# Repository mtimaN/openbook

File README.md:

# openbook

## Overview

# 📚 eBook Reader – System Overview

This project is an eBook reader based on the ESP32-C3 microcontroller. It features a 7.5" E-Ink display, SD card storage, environmental sensing, and a rechargeable LiPo battery, all optimized for low power consumption and readability.

### **ESP32-C3 WROOM**
The main microcontroller that handles:
- Display updates via **SPI**
- File system and memory management
- Button inputs through **GPIO**
- Communication with sensors and RTC via **I2C**
- USB communication for firmware updates or data transfer

### **E-Ink DISPLAY 7.5" 800x400**
- Ultra-low power display ideal for reading in bright light
- Interface: SPI
- Controlled by the ESP32 for rendering text and images

###  Storage

- **SD Card**: Stores eBooks and data files
- **External NOR Flash**: Used for firmware, fonts, or static assets

### Power Management

- **USB-C**: Input for charging and potential USB data connection
- **Battery Charger (MCP73831)**: Manages LiPo charging
- **LiPo Battery**: Powers the system when unplugged
- **Battery Level Monitor (MAX17048G+T10)**: Reports battery percentage to the ESP32
- **3V3 LDO Regulator**: Provides stable 3.3V for the system

### **BME688 Sensor**
- Measures:
  - Temperature
  - Humidity
  - Pressure
  - Air quality
- Data can be displayed or logged for contextual awareness

### **DS3231SN RTC Module**
- Keeps track of time even when powered off
- Useful for:
  - Timestamps
  - Scheduled wake-ups
  - Time-based features
## ⚡ Energy Usage Overview

Estimated average current during typical reading:

| Component        | Avg Current | Notes                             |
|------------------|-------------|-----------------------------------|
| ESP32-C3         | ~2 mA       | Light sleep + brief active use    |
| E-Ink Display    | ~1–2 mA     | Only draws power during refresh   |
| SD Card          | ~1 mA       | Accessed briefly per page turn    |
| BME688 Sensor    | ~0.15 mA    | In low-power mode                 |
| RTC DS3231SN     | ~0.002 mA   | Always running                    |
| Battery Monitor  | ~0.05 mA    | Very low power                    |
| **Total**        | **~5.2 mA** | Approximate average current       |

With a **1200 mAh LiPo battery**:
- **Estimated runtime:** ~**9 days** of light usage
- Based on 1 screen update per minute, minimal background activity

## Bill of Materials (BOM) 
|SAMACSYS_PARTS_USB4110GFA|Value                                                                         |Device                                                                        |Detailed Description                                                                                                                                                                                                                                                                                                                                                                                                                                                                                |Link                                                                                                                         |
|-------------------------|------------------------------------------------------------------------------|------------------------------------------------------------------------------|----------------------------------------------------------------------------------------------------------------------------------------------------------------------------------------------------------------------------------------------------------------------------------------------------------------------------------------------------------------------------------------------------------------------------------------------------------------------------------------------------|-----------------------------------------------------------------------------------------------------------------------------|
|BOOT_BUTTON              |BUTTON_CUSYOMV1                                                               |BUTTON_CUSYOMV1                                                               |                                                                                                                                                                                                                                                                                                                                                                                                                                                                                                    |https://industry.panasonic.com/global/en/products/control/switch/light-touch/number/evqpuj02k                                |
|C1                       |100nF                                                                         |ESP32_WROVER_EAGLE-LTSPICE_CC0402                                             |CAPACITOR, European symbol                                                                                                                                                                                                                                                                                                                                                                                                                                                                          |https://ro.mouser.com/ProductDetail/KYOCERA-AVX/12107C104KAT2A?qs=%252BdQmOuGyFcEpzvTfYF11Tg%3D%3D                           |
|C1_BAT                   |4.7uF                                                                         |ESP32_WROVER_EAGLE-LTSPICE_CC0402                                             |CAPACITOR, European symbol                                                                                                                                                                                                                                                                                                                                                                                                                                                                          |https://ro.mouser.com/ProductDetail/KYOCERA-AVX/12107C104KAT2A?qs=%252BdQmOuGyFcEpzvTfYF11Tg%3D%3D                           |
|C1_BAT1                  |4.7uF                                                                         |ESP32_WROVER_EAGLE-LTSPICE_CC0402                                             |CAPACITOR, European symbol                                                                                                                                                                                                                                                                                                                                                                                                                                                                          |https://ro.mouser.com/ProductDetail/KYOCERA-AVX/12107C104KAT2A?qs=%252BdQmOuGyFcEpzvTfYF11Tg%3D%3D                           |
|C1_BAT2                  |4.7uF                                                                         |EAGLE-LTSPICE_CC0402                                                          |CAPACITOR, European symbol                                                                                                                                                                                                                                                                                                                                                                                                                                                                          |https://ro.mouser.com/ProductDetail/KYOCERA-AVX/12107C104KAT2A?qs=%252BdQmOuGyFcEpzvTfYF11Tg%3D%3D                           |
|C2                       |100nF                                                                         |ESP32_WROVER_EAGLE-LTSPICE_CC0402                                             |CAPACITOR, European symbol                                                                                                                                                                                                                                                                                                                                                                                                                                                                          |https://ro.mouser.com/ProductDetail/KYOCERA-AVX/12107C104KAT2A?qs=%252BdQmOuGyFcEpzvTfYF11Tg%3D%3D                           |
|C2_BAT                   |4.7uF                                                                         |ESP32_WROVER_EAGLE-LTSPICE_CC0402                                             |CAPACITOR, European symbol                                                                                                                                                                                                                                                                                                                                                                                                                                                                          |https://ro.mouser.com/ProductDetail/KYOCERA-AVX/12107C104KAT2A?qs=%252BdQmOuGyFcEpzvTfYF11Tg%3D%3D                           |
|C3                       |100uF TANT                                                                    |RCL_CPOL-EUCT3528                                                             |POLARIZED CAPACITOR, European symbol                                                                                                                                                                                                                                                                                                                                                                                                                                                                |https://ro.mouser.com/ProductDetail/Panasonic/EEU-FS1K101L?qs=sGAEpiMZZMvwFf0viD3Y3fHxNcSaiftwbgqrEa58hlq7Mz20qWHEdw%3D%3D   |
|C4                       |4.7uF/25V                                                                     |ESP32_WROVER_EAGLE-LTSPICE_CC0402                                             |CAPACITOR, European symbol                                                                                                                                                                                                                                                                                                                                                                                                                                                                          |https://ro.mouser.com/ProductDetail/KYOCERA-AVX/12107C104KAT2A?qs=%252BdQmOuGyFcEpzvTfYF11Tg%3D%3D                           |
|C4_USB                   |100nF                                                                         |ESP32_WROVER_EAGLE-LTSPICE_CC0402                                             |CAPACITOR, European symbol                                                                                                                                                                                                                                                                                                                                                                                                                                                                          |https://ro.mouser.com/ProductDetail/KYOCERA-AVX/12107C104KAT2A?qs=%252BdQmOuGyFcEpzvTfYF11Tg%3D%3D                           |
|C5                       |1uF                                                                           |ESP32_WROVER_EAGLE-LTSPICE_CC0402                                             |CAPACITOR, European symbol                                                                                                                                                                                                                                                                                                                                                                                                                                                                          |https://ro.mouser.com/ProductDetail/KYOCERA-AVX/12107C104KAT2A?qs=%252BdQmOuGyFcEpzvTfYF11Tg%3D%3D                           |
|C5_USB                   |4.7uF                                                                         |ESP32_WROVER_EAGLE-LTSPICE_CC0402                                             |CAPACITOR, European symbol                                                                                                                                                                                                                                                                                                                                                                                                                                                                          |https://ro.mouser.com/ProductDetail/KYOCERA-AVX/12107C104KAT2A?qs=%252BdQmOuGyFcEpzvTfYF11Tg%3D%3D                           |
|C6                       |100nF                                                                         |ESP32_WROVER_EAGLE-LTSPICE_CC0402                                             |CAPACITOR, European symbol                                                                                                                                                                                                                                                                                                                                                                                                                                                                          |https://ro.mouser.com/ProductDetail/KYOCERA-AVX/12107C104KAT2A?qs=%252BdQmOuGyFcEpzvTfYF11Tg%3D%3D                           |
|C7                       |10uF                                                                          |ESP32_WROVER_EAGLE-LTSPICE_CC0402                                             |CAPACITOR, European symbol                                                                                                                                                                                                                                                                                                                                                                                                                                                                          |https://ro.mouser.com/ProductDetail/KYOCERA-AVX/12107C104KAT2A?qs=%252BdQmOuGyFcEpzvTfYF11Tg%3D%3D                           |
|C8                       |100nF                                                                         |ESP32_WROVER_EAGLE-LTSPICE_CC0402                                             |CAPACITOR, European symbol                                                                                                                                                                                                                                                                                                                                                                                                                                                                          |https://ro.mouser.com/ProductDetail/KYOCERA-AVX/12107C104KAT2A?qs=%252BdQmOuGyFcEpzvTfYF11Tg%3D%3D                           |
|C9                       |100nF                                                                         |EAGLE-LTSPICE_CC0402                                                          |CAPACITOR, European symbol                                                                                                                                                                                                                                                                                                                                                                                                                                                                          |https://ro.mouser.com/ProductDetail/KYOCERA-AVX/12107C104KAT2A?qs=%252BdQmOuGyFcEpzvTfYF11Tg%3D%3D                           |
|C10                      |100nF                                                                         |ESP32_WROVER_EAGLE-LTSPICE_CC0402                                             |CAPACITOR, European symbol                                                                                                                                                                                                                                                                                                                                                                                                                                                                          |https://ro.mouser.com/ProductDetail/KYOCERA-AVX/12107C104KAT2A?qs=%252BdQmOuGyFcEpzvTfYF11Tg%3D%3D                           |
|C10_SUPERCAP             |CPH3225A                                                                      |CPH3225A                                                                      |Cap 0.011F 3.3V 1210 Flat                                                                                                                                                                                                                                                                                                                                                                                                                                                                           |https://ro.mouser.com/ProductDetail/Seiko-Semiconductors/CPH3225A?qs=3etwrb1wR%252BhUOph6lAO7eg%3D%3D                        |
|CHANGE_BUTTON            |BUTTON_CUSYOMV1                                                               |BUTTON_CUSYOMV1                                                               |                                                                                                                                                                                                                                                                                                                                                                                                                                                                                                    |https://industry.panasonic.com/global/en/products/control/switch/light-touch/number/evqpuj02k                                |
|CHG_LED                  |                                                                              |ADAFRUIT_LEDCHIP-LED0603                                                      |LED                                                                                                                                                                                                                                                                                                                                                                                                                                                                                                 |https://ro.mouser.com/ProductDetail/BJB/35.116.1007-001-01?qs=iLKYxzqNS76jqQb6thkyzg%3D%3D                                   |
|C_DELAY                  |100nF                                                                         |ESP32_WROVER_EAGLE-LTSPICE_CC0402                                             |CAPACITOR, European symbol                                                                                                                                                                                                                                                                                                                                                                                                                                                                          |https://ro.mouser.com/ProductDetail/KYOCERA-AVX/12107C104KAT2A?qs=%252BdQmOuGyFcEpzvTfYF11Tg%3D%3D                           |
|D1                       |USBLC6-2SC6Y                                                                  |USBLC6-2SC6Y                                                                  |Low Cap. ESD Protection Auto SOT-23-6 STMicroelectronics USBLC6-2SC6Y, Dual Uni-Directional TVS Diode Array, 6-Pin SOT-23                                                                                                                                                                                                                                                                                                                                                                           |https://ro.mouser.com/ProductDetail/Nexperia/PMEG6030AEXEX?qs=olJun0bQHM8zqhEtOgE2ZA%3D%3D                                   |
|D2                       |ESP32_WROVER_AVX---SD0805S020S1R0_AVX_SD0805S020S1R0_0_0AVX_SD0805S020S1R0_0_0|ESP32_WROVER_AVX---SD0805S020S1R0_AVX_SD0805S020S1R0_0_0AVX_SD0805S020S1R0_0_0|Schottky Barrier Rectifier Diode                                                                                                                                                                                                                                                                                                                                                                                                                                                                    |https://ro.mouser.com/ProductDetail/Nexperia/PMEG6030AEXEX?qs=olJun0bQHM8zqhEtOgE2ZA%3D%3D                                   |
|D3                       |MBR0530                                                                       |MBR0530                                                                       |ON SEMICONDUCTOR - MBR0530 - DIODE, SCHOTTKY, 0.5A, 30V, SOD-123                                                                                                                                                                                                                                                                                                                                                                                                                                    |https://ro.mouser.com/ProductDetail/Nexperia/PMEG6030AEXEX?qs=olJun0bQHM8zqhEtOgE2ZA%3D%3D                                   |
|D4                       |MBR0530                                                                       |MBR0530                                                                       |ON SEMICONDUCTOR - MBR0530 - DIODE, SCHOTTKY, 0.5A, 30V, SOD-123                                                                                                                                                                                                                                                                                                                                                                                                                                    |https://ro.mouser.com/ProductDetail/Nexperia/PMEG6030AEXEX?qs=olJun0bQHM8zqhEtOgE2ZA%3D%3D                                   |
|D5                       |MBR0530                                                                       |MBR0530                                                                       |ON SEMICONDUCTOR - MBR0530 - DIODE, SCHOTTKY, 0.5A, 30V, SOD-123                                                                                                                                                                                                                                                                                                                                                                                                                                    |https://ro.mouser.com/ProductDetail/Nexperia/PMEG6030AEXEX?qs=olJun0bQHM8zqhEtOgE2ZA%3D%3D                                   |
|D6                       |PGB1010603MR                                                                  |PGB1010603MR                                                                  |Check availability                                                                                                                                                                                                                                                                                                                                                                                                                                                                                  |https://ro.mouser.com/ProductDetail/Nexperia/PMEG6030AEXEX?qs=olJun0bQHM8zqhEtOgE2ZA%3D%3D                                   |
|D7                       |ESP32_WROVER_AVX---SD0805S020S1R0_AVX_SD0805S020S1R0_0_0AVX_SD0805S020S1R0_0_0|ESP32_WROVER_AVX---SD0805S020S1R0_AVX_SD0805S020S1R0_0_0AVX_SD0805S020S1R0_0_0|Schottky Barrier Rectifier Diode                                                                                                                                                                                                                                                                                                                                                                                                                                                                    |https://ro.mouser.com/ProductDetail/Nexperia/PMEG6030AEXEX?qs=olJun0bQHM8zqhEtOgE2ZA%3D%3D                                   |
|D8                       |PGB1010603MR                                                                  |PGB1010603MR                                                                  |Schottky Barrier Rectifier Diode                                                                                                                                                                                                                                                                                                                                                                                                                                                                    |https://ro.mouser.com/ProductDetail/Nexperia/PMEG6030AEXEX?qs=olJun0bQHM8zqhEtOgE2ZA%3D%3D                                   |
|D9                       |PGB1010603MR                                                                  |PGB1010603MR                                                                  |Schottky Barrier Rectifier Diode                                                                                                                                                                                                                                                                                                                                                                                                                                                                    |https://ro.mouser.com/ProductDetail/Nexperia/PMEG6030AEXEX?qs=olJun0bQHM8zqhEtOgE2ZA%3D%3D                                   |
|D10                      |PGB1010603MR                                                                  |PGB1010603MR                                                                  |Schottky Barrier Rectifier Diode                                                                                                                                                                                                                                                                                                                                                                                                                                                                    |https://ro.mouser.com/ProductDetail/Nexperia/PMEG6030AEXEX?qs=olJun0bQHM8zqhEtOgE2ZA%3D%3D                                   |
|D11                      |PGB1010603MR                                                                  |PGB1010603MR                                                                  |Schottky Barrier Rectifier Diode                                                                                                                                                                                                                                                                                                                                                                                                                                                                    |https://ro.mouser.com/ProductDetail/Nexperia/PMEG6030AEXEX?qs=olJun0bQHM8zqhEtOgE2ZA%3D%3D                                   |
|D12                      |PGB1010603MR                                                                  |PGB1010603MR                                                                  |Schottky Barrier Rectifier Diode                                                                                                                                                                                                                                                                                                                                                                                                                                                                    |https://ro.mouser.com/ProductDetail/Nexperia/PMEG6030AEXEX?qs=olJun0bQHM8zqhEtOgE2ZA%3D%3D                                   |
|EPD_C1                   |1uF/50V                                                                       |ESP32_WROVER_EAGLE-LTSPICE_CC0402                                             |CAPACITOR, European symbol                                                                                                                                                                                                                                                                                                                                                                                                                                                                          |https://ro.mouser.com/ProductDetail/KEMET/MMK10105K50A01L4BULK?qs=IKDMbYZLynBqWdM%252BAUSFtw%3D%3D                           |
|EPD_C2                   |1uF/50V                                                                       |ESP32_WROVER_EAGLE-LTSPICE_CC0402                                             |CAPACITOR, European symbol                                                                                                                                                                                                                                                                                                                                                                                                                                                                          |https://ro.mouser.com/ProductDetail/KEMET/MMK10105K50A01L4BULK?qs=IKDMbYZLynBqWdM%252BAUSFtw%3D%3D                           |
|EPD_C5                   |1uF/50V                                                                       |ESP32_WROVER_EAGLE-LTSPICE_CC0402                                             |CAPACITOR, European symbol                                                                                                                                                                                                                                                                                                                                                                                                                                                                          |https://ro.mouser.com/ProductDetail/KEMET/MMK10105K50A01L4BULK?qs=IKDMbYZLynBqWdM%252BAUSFtw%3D%3D                           |
|EPD_C6                   |1uF/50V                                                                       |ESP32_WROVER_EAGLE-LTSPICE_CC0402                                             |CAPACITOR, European symbol                                                                                                                                                                                                                                                                                                                                                                                                                                                                          |https://ro.mouser.com/ProductDetail/KEMET/MMK10105K50A01L4BULK?qs=IKDMbYZLynBqWdM%252BAUSFtw%3D%3D                           |
|EPD_C7                   |1uF/50V                                                                       |ESP32_WROVER_EAGLE-LTSPICE_CC0402                                             |CAPACITOR, European symbol                                                                                                                                                                                                                                                                                                                                                                                                                                                                          |https://ro.mouser.com/ProductDetail/KEMET/MMK10105K50A01L4BULK?qs=IKDMbYZLynBqWdM%252BAUSFtw%3D%3D                           |
|EPD_C8                   |1uF/50V                                                                       |ESP32_WROVER_EAGLE-LTSPICE_CC0402                                             |CAPACITOR, European symbol                                                                                                                                                                                                                                                                                                                                                                                                                                                                          |https://ro.mouser.com/ProductDetail/KEMET/MMK10105K50A01L4BULK?qs=IKDMbYZLynBqWdM%252BAUSFtw%3D%3D                           |
|EPD_C9                   |1uF/50V                                                                       |ESP32_WROVER_EAGLE-LTSPICE_CC0402                                             |CAPACITOR, European symbol                                                                                                                                                                                                                                                                                                                                                                                                                                                                          |https://ro.mouser.com/ProductDetail/KEMET/MMK10105K50A01L4BULK?qs=IKDMbYZLynBqWdM%252BAUSFtw%3D%3D                           |
|EPD_C10                  |1uF/50V                                                                       |ESP32_WROVER_EAGLE-LTSPICE_CC0402                                             |CAPACITOR, European symbol                                                                                                                                                                                                                                                                                                                                                                                                                                                                          |https://ro.mouser.com/ProductDetail/KEMET/MMK10105K50A01L4BULK?qs=IKDMbYZLynBqWdM%252BAUSFtw%3D%3D                           |
|EPD_C11                  |1uF/50V                                                                       |ESP32_WROVER_EAGLE-LTSPICE_CC0402                                             |CAPACITOR, European symbol                                                                                                                                                                                                                                                                                                                                                                                                                                                                          |https://ro.mouser.com/ProductDetail/KEMET/MMK10105K50A01L4BULK?qs=IKDMbYZLynBqWdM%252BAUSFtw%3D%3D                           |
|EPD_C12                  |1uF/50V                                                                       |ESP32_WROVER_EAGLE-LTSPICE_CC0402                                             |CAPACITOR, European symbol                                                                                                                                                                                                                                                                                                                                                                                                                                                                          |https://ro.mouser.com/ProductDetail/KEMET/MMK10105K50A01L4BULK?qs=IKDMbYZLynBqWdM%252BAUSFtw%3D%3D                           |
|IC1                      |BD5229G-TR                                                                    |BD5229G-TR                                                                    |Voltage Detector with Adjustable Delay Time: CMOS processes are utilized to develop high precision, low current consumption CMOS reset ICs that allow arbitrary setting of the delay time. The extensive lineup includes both Nch Open Drain and CMOS output types in a wide range of detection voltages (from 2.3V to 6.0V, in 0.1V steps), enabling selection of the ideal solution based on customer requirements. In addition, the entire series is of course both lead-free and RoHS-compliant.|https://ro.mouser.com/ProductDetail/ROHM-Semiconductor/BD5229G-TR?qs=4kLU8WoGk0vvnhrrYwdszw%3D%3D                            |
|IC4                      |XC6220A331MR-G                                                                |XC6220A331MR-G                                                                |LDO Voltage Regulators                                                                                                                                                                                                                                                                                                                                                                                                                                                                              |                                                                                                                             |
|J1                       |FH34SRJ-24S-0.5SH_99_                                                         |FH34SRJ-24S-0.5SH_99_                                                         |24 Position FFC, FPC Connector Contacts, Top and Bottom 0.020 (0.50mm) Surface Mount, Right Angle"                                                                                                                                                                                                                                                                                                                                                                                                  |                                                                                                                             |
|J2                       |SAMACSYS_PARTS_USB4110-GF-A                                                   |SAMACSYS_PARTS_USB4110-GF-A                                                   |CONN USB 2.0 TYPE-C R/A SMT                                                                                                                                                                                                                                                                                                                                                                                                                                                                         |                                                                                                                             |
|J3                       |QWIIC_RIGHT_ANGLE                                                             |QWIIC_CONNECTORJS-1MM                                                         |SparkFun I2C Standard Qwiic Connector                                                                                                                                                                                                                                                                                                                                                                                                                                                               |                                                                                                                             |
|J4                       |112A-TAAR-R03_ATTEND                                                          |112A-TAAR-R03_ATTEND                                                          |Micro SD Card Socket, Push-Push Type, Top Mount, SMT, H=1.83mm, 10u                                                                                                                                                                                                                                                                                                                                                                                                                                 |                                                                                                                             |
|L1                       |68uH                                                                          |744043680IND_4828-WE-TPC_WRE                                                  |                                                                                                                                                                                                                                                                                                                                                                                                                                                                                                    |                                                                                                                             |
|PFMF.050.1               |ESP32C6_VARISTORCN1812                                                        |ESP32C6_VARISTORCN1812                                                        |VARISTOR                                                                                                                                                                                                                                                                                                                                                                                                                                                                                            |                                                                                                                             |
|Q1                       |20V/4.2A/52mO/1.4W                                                            |ESP32_WROVER_SPARKFUN-DISCRETESEMI_MOSFET_PCH-DMG2305UX-7                     |P-channel MOSFETs                                                                                                                                                                                                                                                                                                                                                                                                                                                                                   |                                                                                                                             |
|Q2                       |20V/4.2A/52mO/1.4W                                                            |ESP32_WROVER_SPARKFUN-DISCRETESEMI_MOSFET_PCH-DMG2305UX-7                     |P-channel MOSFETs                                                                                                                                                                                                                                                                                                                                                                                                                                                                                   |https://ro.mouser.com/ProductDetail/Vishay-Siliconix/SQ3425CEV-T1_GE3?qs=i8QVZAFTkqQazbKSzWc2Vg%3D%3D                        |
|Q3                       |SI1308EDL-T1-GE3                                                              |SI1308EDL-T1-GE3                                                              |MOSFET N-Ch 30V 1.5A TrenchFET SC70 Vishay Si1308EDL-T1-GE3 N-channel MOSFET Transistor, 1.5 A, 30 V, 3-Pin SC-70                                                                                                                                                                                                                                                                                                                                                                                   |https://ro.mouser.com/ProductDetail/Vishay-Semiconductors/SI1308EDL-T1-GE3?qs=bX1%252BNvsK%2FBramh9tgpOaEw%3D%3D             |
|R1                       |10K                                                                           |ESP32_WROVER_EAGLE-LTSPICE_RR0402                                             |RESISTOR, European symbol                                                                                                                                                                                                                                                                                                                                                                                                                                                                           |https://ro.mouser.com/ProductDetail/Vishay-Beyschlag/MCS0402MD4703BE500?qs=sGAEpiMZZMtlubZbdhIBIE4nSA98ICq40rObWhdYP%252BY%3D|
|R1-PINH                  |10K                                                                           |ESP32_WROVER_EAGLE-LTSPICE_RR0402                                             |RESISTOR, European symbol                                                                                                                                                                                                                                                                                                                                                                                                                                                                           |https://ro.mouser.com/ProductDetail/Vishay-Beyschlag/MCS0402MD4703BE500?qs=sGAEpiMZZMtlubZbdhIBIE4nSA98ICq40rObWhdYP%252BY%3D|
|R1-PINH1                 |10K                                                                           |ESP32_WROVER_EAGLE-LTSPICE_RR0402                                             |RESISTOR, European symbol                                                                                                                                                                                                                                                                                                                                                                                                                                                                           |https://ro.mouser.com/ProductDetail/Vishay-Beyschlag/MCS0402MD4703BE500?qs=sGAEpiMZZMtlubZbdhIBIE4nSA98ICq40rObWhdYP%252BY%3D|
|R1_BAT                   |200                                                                           |ESP32_WROVER_EAGLE-LTSPICE_RR0402                                             |RESISTOR, European symbol                                                                                                                                                                                                                                                                                                                                                                                                                                                                           |https://ro.mouser.com/ProductDetail/Vishay-Beyschlag/MCS0402MD4703BE500?qs=sGAEpiMZZMtlubZbdhIBIE4nSA98ICq40rObWhdYP%252BY%3D|
|R1_PWRUSB                |100K                                                                          |ESP32_WROVER_EAGLE-LTSPICE_RR0402                                             |RESISTOR, European symbol                                                                                                                                                                                                                                                                                                                                                                                                                                                                           |https://ro.mouser.com/ProductDetail/Vishay-Beyschlag/MCS0402MD4703BE500?qs=sGAEpiMZZMtlubZbdhIBIE4nSA98ICq40rObWhdYP%252BY%3D|
|R2                       |2.2                                                                           |ESP32_WROVER_EAGLE-LTSPICE_RR0402                                             |RESISTOR, European symbol                                                                                                                                                                                                                                                                                                                                                                                                                                                                           |https://ro.mouser.com/ProductDetail/Vishay-Beyschlag/MCS0402MD4703BE500?qs=sGAEpiMZZMtlubZbdhIBIE4nSA98ICq40rObWhdYP%252BY%3D|
|R2-PINH                  |10K                                                                           |ESP32_WROVER_EAGLE-LTSPICE_RR0402                                             |RESISTOR, European symbol                                                                                                                                                                                                                                                                                                                                                                                                                                                                           |https://ro.mouser.com/ProductDetail/Vishay-Beyschlag/MCS0402MD4703BE500?qs=sGAEpiMZZMtlubZbdhIBIE4nSA98ICq40rObWhdYP%252BY%3D|
|R2-PINH1                 |10K                                                                           |ESP32_WROVER_EAGLE-LTSPICE_RR0402                                             |RESISTOR, European symbol                                                                                                                                                                                                                                                                                                                                                                                                                                                                           |https://ro.mouser.com/ProductDetail/Vishay-Beyschlag/MCS0402MD4703BE500?qs=sGAEpiMZZMtlubZbdhIBIE4nSA98ICq40rObWhdYP%252BY%3D|
|R2-USB                   |5k1                                                                           |ESP32_WROVER_EAGLE-LTSPICE_RR0402                                             |RESISTOR, European symbol                                                                                                                                                                                                                                                                                                                                                                                                                                                                           |https://ro.mouser.com/ProductDetail/Vishay-Beyschlag/MCS0402MD4703BE500?qs=sGAEpiMZZMtlubZbdhIBIE4nSA98ICq40rObWhdYP%252BY%3D|
|R2-USB1                  |5k1                                                                           |ESP32_WROVER_EAGLE-LTSPICE_RR0402                                             |RESISTOR, European symbol                                                                                                                                                                                                                                                                                                                                                                                                                                                                           |https://ro.mouser.com/ProductDetail/Vishay-Beyschlag/MCS0402MD4703BE500?qs=sGAEpiMZZMtlubZbdhIBIE4nSA98ICq40rObWhdYP%252BY%3D|
|R2_BAT                   |2K                                                                            |ESP32_WROVER_EAGLE-LTSPICE_RR0402                                             |RESISTOR, European symbol                                                                                                                                                                                                                                                                                                                                                                                                                                                                           |https://ro.mouser.com/ProductDetail/Vishay-Beyschlag/MCS0402MD4703BE500?qs=sGAEpiMZZMtlubZbdhIBIE4nSA98ICq40rObWhdYP%252BY%3D|
|R3                       |10K                                                                           |ESP32_WROVER_EAGLE-LTSPICE_RR0402                                             |RESISTOR, European symbol                                                                                                                                                                                                                                                                                                                                                                                                                                                                           |https://ro.mouser.com/ProductDetail/Vishay-Beyschlag/MCS0402MD4703BE500?qs=sGAEpiMZZMtlubZbdhIBIE4nSA98ICq40rObWhdYP%252BY%3D|
|R4                       |10K                                                                           |ESP32_WROVER_EAGLE-LTSPICE_RR0402                                             |RESISTOR, European symbol                                                                                                                                                                                                                                                                                                                                                                                                                                                                           |https://ro.mouser.com/ProductDetail/Vishay-Beyschlag/MCS0402MD4703BE500?qs=sGAEpiMZZMtlubZbdhIBIE4nSA98ICq40rObWhdYP%252BY%3D|
|R5                       |10K                                                                           |ESP32_WROVER_EAGLE-LTSPICE_RR0402                                             |RESISTOR, European symbol                                                                                                                                                                                                                                                                                                                                                                                                                                                                           |https://ro.mouser.com/ProductDetail/Vishay-Beyschlag/MCS0402MD4703BE500?qs=sGAEpiMZZMtlubZbdhIBIE4nSA98ICq40rObWhdYP%252BY%3D|
|R6                       |10K                                                                           |ESP32_WROVER_EAGLE-LTSPICE_RR0402                                             |RESISTOR, European symbol                                                                                                                                                                                                                                                                                                                                                                                                                                                                           |https://ro.mouser.com/ProductDetail/Vishay-Beyschlag/MCS0402MD4703BE500?qs=sGAEpiMZZMtlubZbdhIBIE4nSA98ICq40rObWhdYP%252BY%3D|
|R7                       |10K                                                                           |ESP32_WROVER_EAGLE-LTSPICE_RR0402                                             |RESISTOR, European symbol                                                                                                                                                                                                                                                                                                                                                                                                                                                                           |https://ro.mouser.com/ProductDetail/Vishay-Beyschlag/MCS0402MD4703BE500?qs=sGAEpiMZZMtlubZbdhIBIE4nSA98ICq40rObWhdYP%252BY%3D|
|R8                       |10K                                                                           |ESP32_WROVER_EAGLE-LTSPICE_RR0402                                             |RESISTOR, European symbol                                                                                                                                                                                                                                                                                                                                                                                                                                                                           |https://ro.mouser.com/ProductDetail/Vishay-Beyschlag/MCS0402MD4703BE500?qs=sGAEpiMZZMtlubZbdhIBIE4nSA98ICq40rObWhdYP%252BY%3D|
|R9                       |10K                                                                           |ESP32_WROVER_EAGLE-LTSPICE_RR0402                                             |RESISTOR, European symbol                                                                                                                                                                                                                                                                                                                                                                                                                                                                           |https://ro.mouser.com/ProductDetail/Vishay-Beyschlag/MCS0402MD4703BE500?qs=sGAEpiMZZMtlubZbdhIBIE4nSA98ICq40rObWhdYP%252BY%3D|
|R10                      |10K                                                                           |ESP32_WROVER_EAGLE-LTSPICE_RR0402                                             |RESISTOR, European symbol                                                                                                                                                                                                                                                                                                                                                                                                                                                                           |https://ro.mouser.com/ProductDetail/Vishay-Beyschlag/MCS0402MD4703BE500?qs=sGAEpiMZZMtlubZbdhIBIE4nSA98ICq40rObWhdYP%252BY%3D|
|RESET_BUTTON             |BUTTON_CUSYOMV1                                                               |BUTTON_CUSYOMV1                                                               |                                                                                                                                                                                                                                                                                                                                                                                                                                                                                                    |https://industry.panasonic.com/global/en/products/control/switch/light-touch/number/evqpuj02k                                |
|R_BOOT                   |10K                                                                           |ESP32_WROVER_EAGLE-LTSPICE_RR0402                                             |RESISTOR, European symbol                                                                                                                                                                                                                                                                                                                                                                                                                                                                           |https://ro.mouser.com/ProductDetail/Vishay-Beyschlag/MCS0402MD4703BE500?qs=sGAEpiMZZMtlubZbdhIBIE4nSA98ICq40rObWhdYP%252BY%3D|
|R_CAPACITOR              |15                                                                            |ESP32_WROVER_EAGLE-LTSPICE_RR0402                                             |RESISTOR, European symbol                                                                                                                                                                                                                                                                                                                                                                                                                                                                           |https://ro.mouser.com/ProductDetail/Vishay-Beyschlag/MCS0402MD4703BE500?qs=sGAEpiMZZMtlubZbdhIBIE4nSA98ICq40rObWhdYP%252BY%3D|
|R_CHANGE                 |10K                                                                           |ESP32_WROVER_EAGLE-LTSPICE_RR0402                                             |RESISTOR, European symbol                                                                                                                                                                                                                                                                                                                                                                                                                                                                           |https://ro.mouser.com/ProductDetail/Vishay-Beyschlag/MCS0402MD4703BE500?qs=sGAEpiMZZMtlubZbdhIBIE4nSA98ICq40rObWhdYP%252BY%3D|
|R_CL1                    |10K                                                                           |ESP32_WROVER_EAGLE-LTSPICE_RR0402                                             |RESISTOR, European symbol                                                                                                                                                                                                                                                                                                                                                                                                                                                                           |https://ro.mouser.com/ProductDetail/Vishay-Beyschlag/MCS0402MD4703BE500?qs=sGAEpiMZZMtlubZbdhIBIE4nSA98ICq40rObWhdYP%252BY%3D|
|R_RESET                  |10K                                                                           |ESP32_WROVER_EAGLE-LTSPICE_RR0402                                             |RESISTOR, European symbol                                                                                                                                                                                                                                                                                                                                                                                                                                                                           |https://ro.mouser.com/ProductDetail/Vishay-Beyschlag/MCS0402MD4703BE500?qs=sGAEpiMZZMtlubZbdhIBIE4nSA98ICq40rObWhdYP%252BY%3D|
|SENSOR2                  |                                                                              |ESP32_WROVER_BME680_BME680                                                    |Integrated Environmental Unit                                                                                                                                                                                                                                                                                                                                                                                                                                                                       |https://ro.mouser.com/ProductDetail/Bosch-Sensortec/BME680?qs=v271MhAjFHjo0yA%2FC4OnDQ%3D%3D                                 |
|SJ1                      |                                                                              |SJ                                                                            |SMD solder JUMPER                                                                                                                                                                                                                                                                                                                                                                                                                                                                                   |https://ro.mouser.com/ProductDetail/Nidec-Components/CJS-1201B?qs=XeJtXLiO41SSSa2Z7HG9Iw%3D%3D                               |
|TP1                      |TPTP20R                                                                       |TPTP20R                                                                       |Test pad                                                                                                                                                                                                                                                                                                                                                                                                                                                                                            |                                                                                                                             |
|TP2                      |TPTP20R                                                                       |TPTP20R                                                                       |Test pad                                                                                                                                                                                                                                                                                                                                                                                                                                                                                            |                                                                                                                             |
|TP3                      |TPTP20R                                                                       |TPTP20R                                                                       |Test pad                                                                                                                                                                                                                                                                                                                                                                                                                                                                                            |                                                                                                                             |
|TP4                      |TPTP20R                                                                       |TPTP20R                                                                       |Test pad                                                                                                                                                                                                                                                                                                                                                                                                                                                                                            |                                                                                                                             |
|TP5                      |TPTP20R                                                                       |TPTP20R                                                                       |Test pad                                                                                                                                                                                                                                                                                                                                                                                                                                                                                            |                                                                                                                             |
|TP6                      |TPTP20R                                                                       |TPTP20R                                                                       |Test pad                                                                                                                                                                                                                                                                                                                                                                                                                                                                                            |                                                                                                                             |
|TP7                      |TPTP20R                                                                       |TPTP20R                                                                       |Test pad                                                                                                                                                                                                                                                                                                                                                                                                                                                                                            |                                                                                                                             |
|TP8                      |TPTP20R                                                                       |TPTP20R                                                                       |Test pad                                                                                                                                                                                                                                                                                                                                                                                                                                                                                            |                                                                                                                             |
|TP9                      |TPTP20R                                                                       |TPTP20R                                                                       |Test pad                                                                                                                                                                                                                                                                                                                                                                                                                                                                                            |                                                                                                                             |
|TP10                     |TPTP20R                                                                       |TPTP20R                                                                       |Test pad                                                                                                                                                                                                                                                                                                                                                                                                                                                                                            |                                                                                                                             |
|TP11                     |TPTP20R                                                                       |TPTP20R                                                                       |Test pad                                                                                                                                                                                                                                                                                                                                                                                                                                                                                            |                                                                                                                             |
|TP12                     |TPTP20R                                                                       |TPTP20R                                                                       |Test pad                                                                                                                                                                                                                                                                                                                                                                                                                                                                                            |                                                                                                                             |
|TP13                     |TPTP20R                                                                       |TPTP20R                                                                       |Test pad                                                                                                                                                                                                                                                                                                                                                                                                                                                                                            |                                                                                                                             |
|TP14                     |TPTP20R                                                                       |TPTP20R                                                                       |Test pad                                                                                                                                                                                                                                                                                                                                                                                                                                                                                            |                                                                                                                             |
|TP15                     |TPTP20R                                                                       |TPTP20R                                                                       |Test pad                                                                                                                                                                                                                                                                                                                                                                                                                                                                                            |                                                                                                                             |
|TP16                     |TPTP20R                                                                       |TPTP20R                                                                       |Test pad                                                                                                                                                                                                                                                                                                                                                                                                                                                                                            |                                                                                                                             |
|TP17                     |TPTP20R                                                                       |TPTP20R                                                                       |Test pad                                                                                                                                                                                                                                                                                                                                                                                                                                                                                            |                                                                                                                             |
|U1                       |W25Q512JVEIQ                                                                  |W25Q512JVEIQ                                                                  |                                                                                                                                                                                                                                                                                                                                                                                                                                                                                                    |https://ro.mouser.com/ProductDetail/Winbond/W25Q512JVEIQ?qs=l7cgNqFNU1jw6svr3at6tA%3D%3D                                     |
|U2                       |ESP32-C6-WROOM-1-N8                                                           |ESP32-C6-WROOM-1-N8                                                           |                                                                                                                                                                                                                                                                                                                                                                                                                                                                                                    |https://ro.mouser.com/ProductDetail/Espressif-Systems/ESP32-C6-WROOM-1-N8?qs=8Wlm6%252BaMh8ST02Gmwp74cw%3D%3D                |
|U3                       |DS3231SN#                                                                     |DS3231SN#                                                                     |                                                                                                                                                                                                                                                                                                                                                                                                                                                                                                    |https://ro.mouser.com/ProductDetail/Analog-Devices-Maxim-Integrated/DS3231SN?qs=1eQvB6Dk1vhUlr8%2FOrV0Fw%3D%3D               |
|U4                       |MAX17048G+T10                                                                 |MAX17048G+T10                                                                 |                                                                                                                                                                                                                                                                                                                                                                                                                                                                                                    |https://ro.mouser.com/ProductDetail/Analog-Devices-Maxim-Integrated/MAX17048G%2bT10?qs=D7PJwyCwLAoGnnn8jEPRBQ%3D%3D          |
|U5                       |MCP73831                                                                      |ESP32_WROVER_SPARKFUN-IC-POWER_MCP73831                                       |MCP73831T Li-Ion, Li-Pol Controller                                                                                                                                                                                                                                                                                                                                                                                                                                                                 |https://ro.mouser.com/ProductDetail/Microchip-Technology/MCP73831T-2ACI-OT?qs=yUQqVecv4qvbBQBGbHx0Mw%3D%3D                   |

## Detailed description

- Resistor (R1) connected to GPIO8: This is a pull-up resistor connected to GPIO8. Pull-up resistors are used to ensure a pin has a defined high state when no external signal is applied.
- GPIO8: This is a general-purpose input/output pin. It can be configured as either an input or an output.
- IO/BOOT (Pin 15): This pin is used to put the ESP32-C6 into bootloader mode, which is necessary for flashing firmware.
- NC (Pin 22): This stands for "No Connection." This pin is not connected to anything in this particular circuit.
- EN (Pin 3): This is the Enable pin. Pulling this pin low resets the ESP32-C6.
- INT_RTC (Pin 8): This is likely an interrupt pin related to the Real-Time Clock (RTC) functionality.
- 32KHz (Pin 9): This is probably the input for a 32.768 kHz crystal oscillator, which is used for the RTC.
- MISO (Pin 27): This is the Master In Slave Out pin for the SPI (Serial Peripheral Interface) communication protocol.
- EPD_BUSY (Pin 4): This pin is likely used to signal the busy state of an E-Paper Display (EPD).
- SS_SD (Pin 5): This is the Slave Select pin for the SD card interface.
- EPD_DC (Pin 6): This is the Data/Command pin for the EPD.
- SCK (Pin 7): This is the Serial Clock pin for SPI communication.
- MOSI (Pin 10): This is the Master Out Slave In pin for SPI communication.
- 3V3 (Pin 2): This is another 3.3V power supply pin.
- IO10 to IO15 (Pins 11-14, 23): These are general-purpose input/output pins.
- TXD0/GPIO16 (Pin 24): This is the transmit pin for UART0 (Universal Asynchronous Receiver/Transmitter) and also functions as GPIO16.
- RXD0/GPIO17 (Pin 25): This is the receive pin for UART0 and also functions as GPIO17.
- RX (Pin 16): This is likely another receive pin, possibly for a second UART.
- RTC_RST (Pin 17): This is the reset pin for the RTC.
- I2C_PW (Pin 12): This pin might be related to powering the I2C (Inter-Integrated Circuit) bus.
- IO18 to IO23 (Pins 18-21): These are general-purpose input/output pins.
- EPD_3V3_C (Pin 19): This is likely a 3.3V power supply pin specifically for the EPD.
- SDA (Pin 20): This is the Serial Data pin for I2C communication.
- SCL (Pin 21): This is the Serial Clock pin for I2C communication.
- EPD_RST (Pin 21): This is the reset pin for the EPD.
- 1*11 (Pin 1): This indicates that pin 1 is connected to ground (GND).

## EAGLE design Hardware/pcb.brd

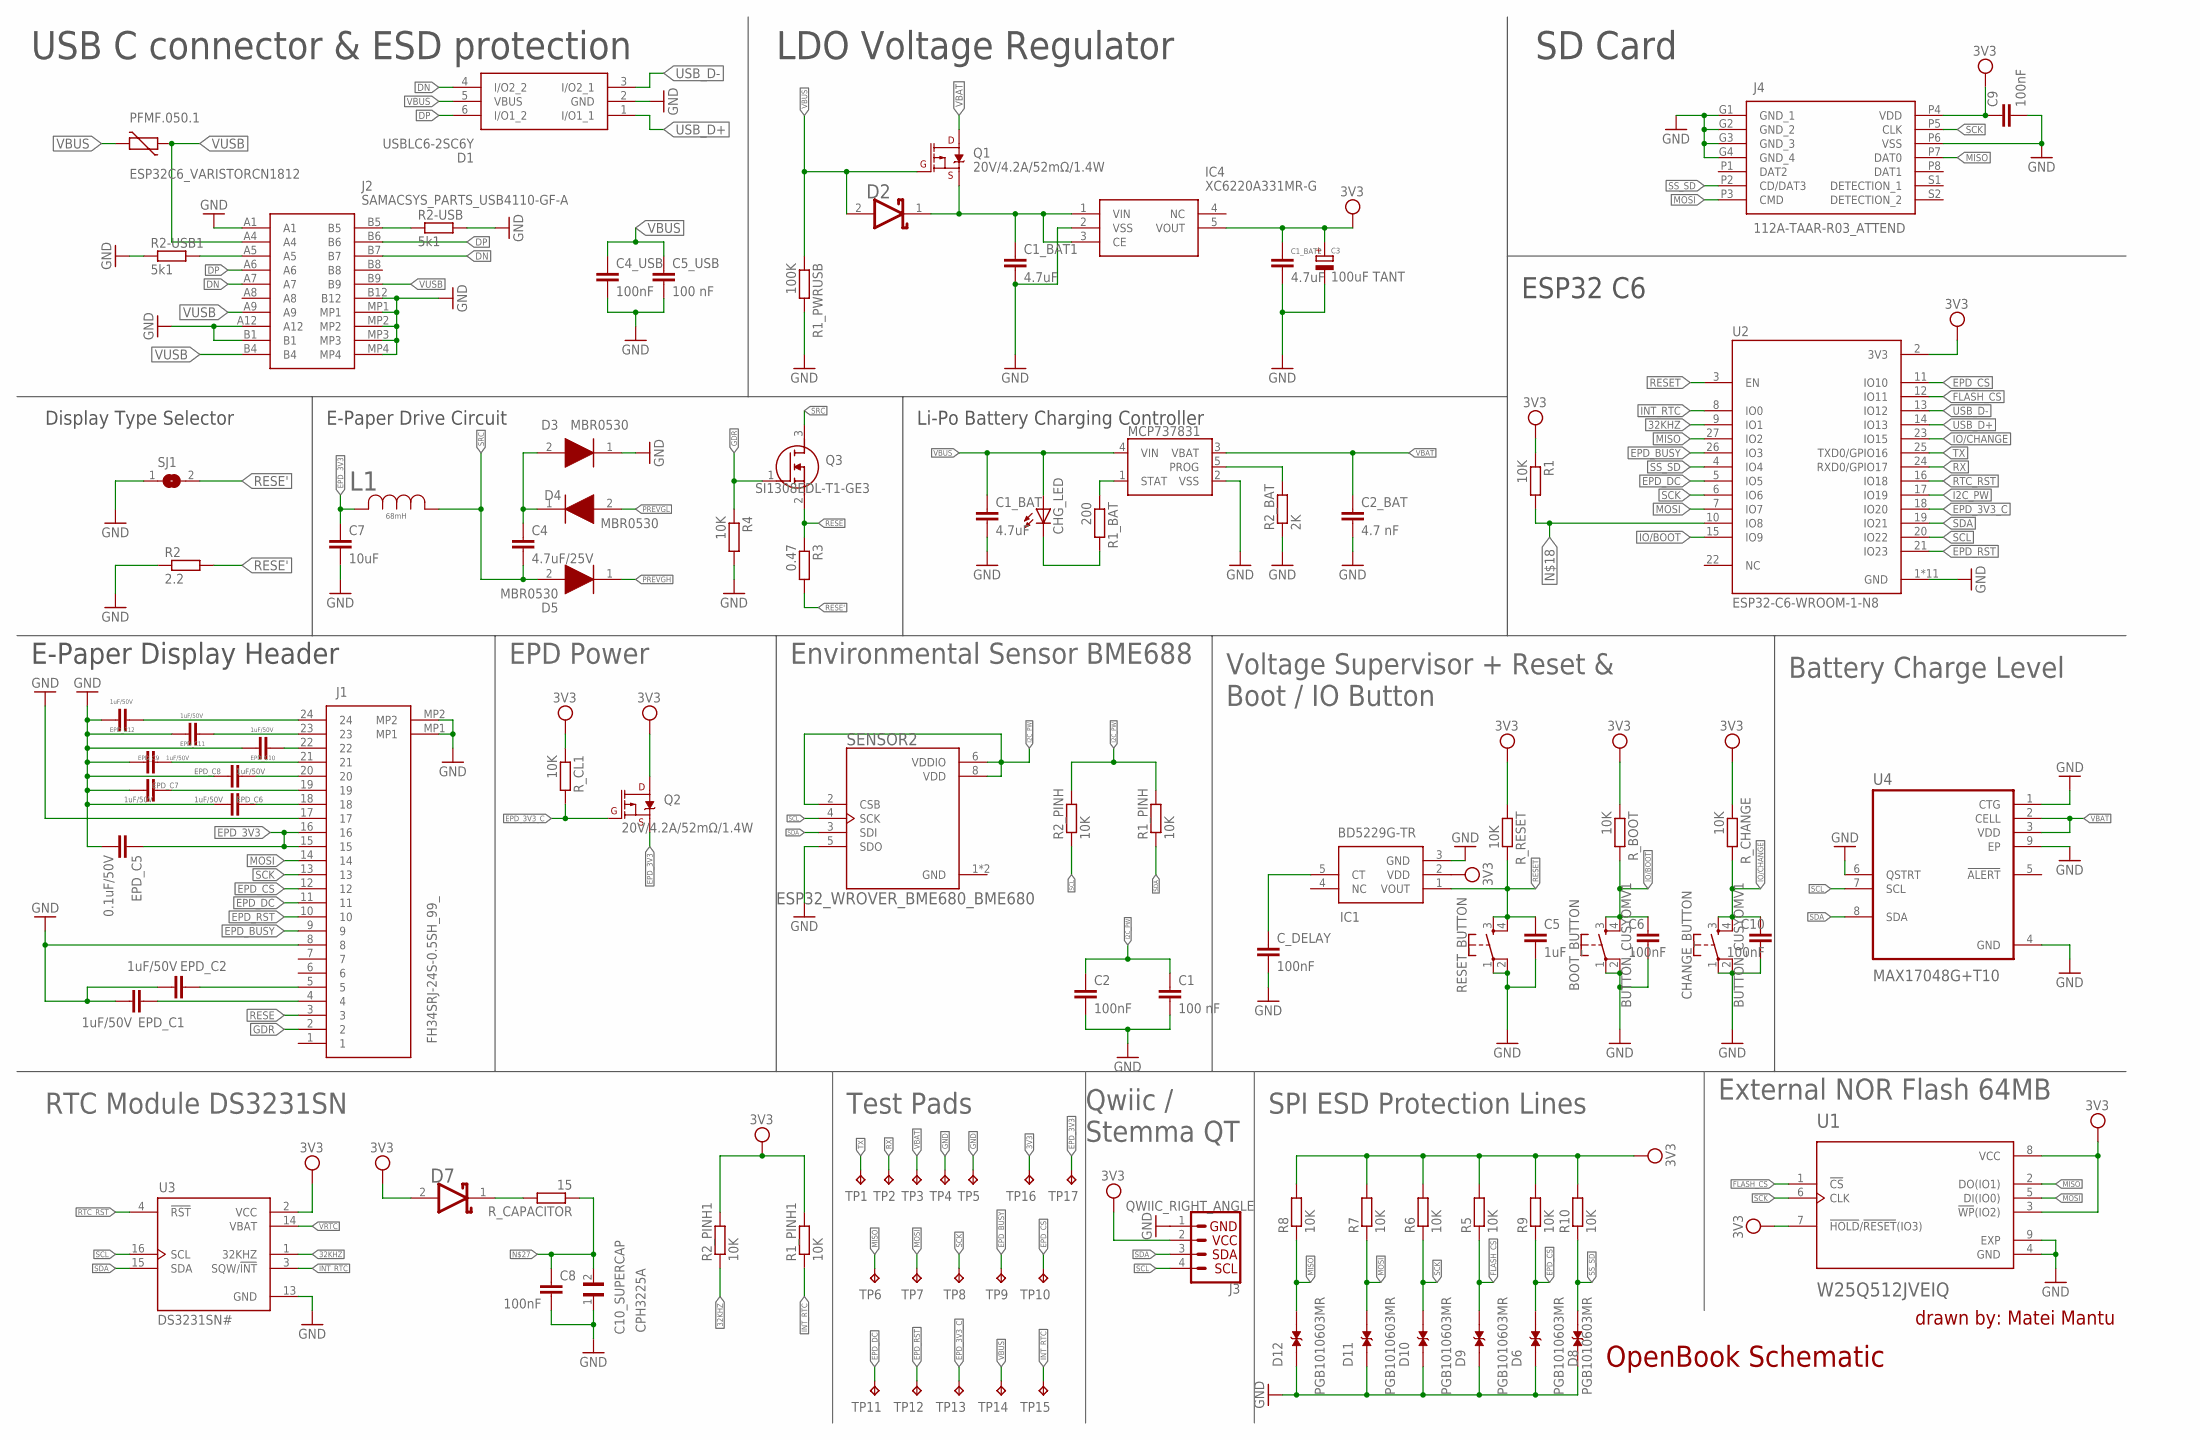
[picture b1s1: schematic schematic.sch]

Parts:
BOOT_BUTTON: BUTTON_CUSYOMV1; MYBUTTON
C1, C5_USB: 100 nF; EAGLE-LTSPICE_C0402
C1_BAT, C1_BAT1, C1_BAT2: 4.7uF; EAGLE-LTSPICE_C0402
C2, C4_USB, C6, C8, C9, C10: 100nF; EAGLE-LTSPICE_C0402
C2_BAT: 4.7 nF; EAGLE-LTSPICE_C0402
C3: 100uF TANT; RCL_CT3528
C4: 4.7uF/25V; EAGLE-LTSPICE_C0402
C5: 1uF; EAGLE-LTSPICE_C0402
C7: 10uF; EAGLE-LTSPICE_C0402
C10_SUPERCAP: CPH3225A; CAPCP3225X100N
CHANGE_BUTTON: BUTTON_CUSYOMV1; MYBUTTON
CHG_LED: ADAFRUIT_LEDCHIP-LED0603; ADAFRUIT_CHIP-LED0603
C_DELAY: 100nF; EAGLE-LTSPICE_C0402
D1: USBLC6-2SC6Y; SOT95P280X145-6N
D2, D7: ESP32_WROVER_AVX---SD0805S020S1R0_AVX_SD0805S020S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; ESP32_WROVER_AVX---SD0805S020S1R0_AVX_SD0805S020S1R0_0
D3, D4, D5: MBR0530; SOD3716X135N
D6, D8, D9, D10, D11, D12: PGB1010603MR; DIOC1608X36N
EPD_C1, EPD_C2, EPD_C6, EPD_C7, EPD_C8, EPD_C9, EPD_C10, EPD_C11, EPD_C12: 1uF/50V; EAGLE-LTSPICE_C0402
EPD_C5: 0.1uF/50V; EAGLE-LTSPICE_C0402
IC1: BD5229G-TR; SOT95P280X125-5N
IC4: XC6220A331MR-G; SOT95P280X120-5N
J1: FH34SRJ-24S-0.5SH_99_; FH34SRJ24S05SH99
J2: SAMACSYS_PARTS_USB4110-GF-A; SAMACSYS_PARTS_USB4110GFA
J3: QWIIC_RIGHT_ANGLE; JST04_1MM_RA
J4: 112A-TAAR-R03_ATTEND; 112ATAARR03ATTEND
L1: 68mH; IND_4828-WE-TPC_WRE
MCP737831: ESP32_WROVER_SPARKFUN-IC-POWER_MCP73831; ESP32_WROVER_SPARKFUN-IC-POWER_SOT23-5
PFMF.050.1: ESP32C6_VARISTORCN1812; ESP32C6_VARISTOR_CT/CN1812
Q1, Q2: 20V/4.2A/52mΩ/1.4W; ESP32_WROVER_SPARKFUN-DISCRETESEMI_SOT23-3
Q3: SI1308EDL-T1-GE3; SOT65P210X110-3N
R1, R1_PINH, R1_PINH1, R2_PINH, R2_PINH1, R4, R5, R6, R7, R8, R9, R10: 10K; ESP32_WROVER_EAGLE-LTSPICE_R0402
R1_BAT: 200; ESP32_WROVER_EAGLE-LTSPICE_R0402
R1_PWRUSB: 100K; ESP32_WROVER_EAGLE-LTSPICE_R0402
R2: 2.2; ESP32_WROVER_EAGLE-LTSPICE_R0402
R2-USB, R2-USB1: 5k1; ESP32_WROVER_EAGLE-LTSPICE_R0402
R2_BAT: 2K; ESP32_WROVER_EAGLE-LTSPICE_R0402
R3: 0.47; ESP32_WROVER_EAGLE-LTSPICE_R0402
RESET_BUTTON: BUTTON_CUSYOMV1; MYBUTTON
R_BOOT: 10K; ESP32_WROVER_EAGLE-LTSPICE_R0402
R_CAPACITOR: 15; ESP32_WROVER_EAGLE-LTSPICE_R0402
R_CHANGE: 10K; ESP32_WROVER_EAGLE-LTSPICE_R0402
R_CL1: 10K; ESP32_WROVER_EAGLE-LTSPICE_R0402
R_RESET: 10K; ESP32_WROVER_EAGLE-LTSPICE_R0402
SENSOR2: ESP32_WROVER_BME680_BME680; ESP32_WROVER_BME680_PSON80P300X300X100-8N
SJ1: SJ
TP1, TP2, TP3, TP4, TP5, TP6, TP7, TP8, TP9, TP10, TP11, TP12, TP13, TP14, TP15, TP16, TP17: TPTP20R; TP20R
U1: W25Q512JVEIQ; SON127P600X800X80-9N
U2: ESP32-C6-WROOM-1-N8; XCVR_ESP32-C6-WROOM-1-N8
U3: DS3231SN#; SOIC127P1032X265-16N
U4: MAX17048G+T10; SON50P200X200X80-9N

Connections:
3V3: C1_BAT2.1, C3.+, C9.1, D7.2 (ANODE), IC1.2 (VDD), IC4.5 (VOUT), J3.2, J4.P4 (VDD), Q2.3 (D), R1.1, R1_PINH1.2, R2_PINH1.2, R5.2, R6.2, R7.2, R8.2, R9.2, R10.2, R_BOOT.1, R_CHANGE.1, R_CL1.1, R_RESET.1, TP16.TP, U1.3 (!WP!(IO2)), U1.7 (!HOLD!/!RESET!(IO3)), U1.8 (VCC), U2.2 (3V3), U3.2 (VCC)
32KHZ: R2_PINH1.1, U2.9 (IO1), U3.1 (32KHZ)
DN: D1.4 (I/O2_2), J2.A7, J2.B7
DP: D1.6 (I/O1_2), J2.A6, J2.B6
EPD_3V3: C7.1, EPD_C5.1, J1.15, J1.16, L1.2, Q2.2 (S), TP17.TP
EPD_3V3_C: Q2.1 (G), R_CL1.2, TP13.TP, U2.18 (IO20)
EPD_BUSY: J1.9, TP9.TP, U2.26 (IO3)
EPD_CS: D6.2, J1.12, R9.1, TP10.TP, U2.11 (IO10)
EPD_DC: J1.11, TP11.TP, U2.5 (IO5)
EPD_RST: J1.10, TP12.TP, U2.21 (IO23)
FLASH_CS: D9.2, R5.1, U1.1 (!CS), U2.12 (IO11)
GDR: J1.2, Q3.1 (G), R4.1
GND: BOOT_BUTTON.1, BOOT_BUTTON.2, C1.2, C1_BAT.2, C1_BAT1.2, C1_BAT2.2, C2.2, C2_BAT.2, C3.-, C4_USB.2, C5.2, C5_USB.2, C6.2, C7.2, C8.2, C9.2, C10.2, C10_SUPERCAP.1, CHANGE_BUTTON.1, CHANGE_BUTTON.2, C_DELAY.2, D1.2 (GND), D3.1 (K), D6.1, D8.1, D9.1, D10.1, D11.1, D12.1, EPD_C5.2, EPD_C6.2, EPD_C7.2, EPD_C8.2, EPD_C9.2, EPD_C10.2, EPD_C11.2, EPD_C12.2, IC1.3 (GND), IC4.2 (VSS), J1.17, J1.MP1, J1.MP2, J2.A1, J2.A12, J2.B1, J2.B12, J2.MP1, J2.MP2, J2.MP3, J2.MP4, J3.1, J4.G1 (GND_1), J4.G2 (GND_2), J4.G3 (GND_3), J4.G4 (GND_4), J4.P6 (VSS), MCP737831.2 (VSS), R1_PWRUSB.2, R2.1, R2-USB.2, R2-USB1.1, R2_BAT.1, R4.2, RESET_BUTTON.1, RESET_BUTTON.2, SENSOR2.1 (GND), SENSOR2.5 (SDO), SENSOR2.7 (GND), SJ1.1, TP4.TP, TP5.TP, U1.4 (GND), U1.9 (EXP), U2.1 (GND), U2.28 (GND), U2.29_1 (GND), U2.29_2 (GND), U2.29_3 (GND), U2.29_4 (GND), U2.29_5 (GND), U2.29_6 (GND), U2.29_7 (GND), U2.29_8 (GND), U2.29_9 (GND), U3.13 (GND), U4.1 (CTG), U4.4 (GND), U4.6 (QSTRT), U4.9 (EP)
I2C_PW: C1.1, C2.1, R1_PINH.2, R2_PINH.2, SENSOR2.2 (CSB), SENSOR2.6 (VDDIO), SENSOR2.8 (VDD), U2.17 (IO19)
INT_RTC: R1_PINH1.1, TP15.TP, U2.8 (IO0), U3.3 (SQW/!INT)
IO/BOOT: BOOT_BUTTON.3, BOOT_BUTTON.4, C6.1, R_BOOT.2, U2.15 (IO9)
IO/CHANGE: C10.1, CHANGE_BUTTON.3, CHANGE_BUTTON.4, R_CHANGE.2, U2.23 (IO15)
MISO: D12.2, J4.P7 (DAT0), R8.1, TP6.TP, U1.2 (DO(IO1)), U2.27 (IO2)
MOSI: D11.2, J1.14, J4.P3 (CMD), R7.1, TP7.TP, U1.5 (DI(IO0)), U2.7 (IO7)
unnamed: C1_BAT1.1, D2.1 (CATHODE), IC4.1 (VIN), IC4.3 (CE), Q1.2 (S)
unnamed: EPD_C12.1, J1.24
unnamed: J2.A5, R2-USB1.2
unnamed: CHG_LED.C, R1_BAT.2
unnamed: C4.1, D3.2 (A), D4.1 (K)
unnamed: MCP737831.1 (STAT), R1_BAT.1
unnamed: MCP737831.5 (PROG), R2_BAT.2
unnamed: EPD_C11.1, J1.23
unnamed: J2.B5, R2-USB.1
unnamed: EPD_C10.1, J1.22
unnamed: EPD_C9.1, J1.21
unnamed: EPD_C8.1, J1.20
unnamed: EPD_C7.1, J1.19
unnamed: EPD_C6.1, J1.18
unnamed: C_DELAY.1, IC1.5 (CT)
unnamed: R1.2, U2.10 (IO8)
unnamed: EPD_C1.2, EPD_C2.2, J1.8
unnamed: EPD_C1.1, J1.4
unnamed: EPD_C2.1, J1.5
unnamed: D7.1 (CATHODE), R_CAPACITOR.2
unnamed: C8.1, C10_SUPERCAP.2, R_CAPACITOR.1
PREVGH: D5.1 (K)
PREVGL: D4.2 (A)
RESE: J1.3, Q3.2 (S), R3.1
RESE': R2.2, R3.2, SJ1.2
RESET: C5.1, IC1.1 (VOUT), RESET_BUTTON.3, RESET_BUTTON.4, R_RESET.2, U2.3 (EN)
RTC_RST: U2.16 (IO18), U3.4 (!RST)
RX: TP2.TP, U2.24 (RXD0/GPIO17)
SCK: D10.2, J1.13, J4.P5 (CLK), R6.1, TP8.TP, U1.6 (CLK), U2.6 (IO6)
SCL: J3.4, R2_PINH.1, SENSOR2.4 (SCK), U2.20 (IO22), U3.16 (SCL), U4.7 (SCL)
SDA: J3.3, R1_PINH.1, SENSOR2.3 (SDI), U2.19 (IO21), U3.15 (SDA), U4.8 (SDA)
SRC: C4.2, D5.2 (A), L1.1, Q3.3 (D)
SS_SD: D8.2, J4.P2 (CD/DAT3), R10.1, U2.4 (IO4)
TX: TP1.TP, U2.25 (TXD0/GPIO16)
USB_D+: D1.1 (I/O1_1), U2.14 (IO13)
USB_D-: D1.3 (I/O2_1), U2.13 (IO12)
VBAT: C2_BAT.1, MCP737831.3 (VBAT), Q1.3 (D), TP3.TP, U4.2 (CELL), U4.3 (VDD)
VBUS: C1_BAT.1, C4_USB.1, C5_USB.1, CHG_LED.A, D1.5 (VBUS), D2.2 (ANODE), MCP737831.4 (VIN), PFMF.050.1.2, Q1.1 (G), R1_PWRUSB.1, TP14.TP
VRTC: U3.14 (VBAT)
VUSB: J2.A4, J2.A9, J2.B4, J2.B9, PFMF.050.1.1

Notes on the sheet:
USB C connector & ESD protection
LDO Voltage Regulator
SD Card
Display Type Selector
E-Paper Drive Circuit
Li-Po Battery Charging Controller
ESP32 C6
E-Paper Display Header
EPD Power
Environmental Sensor BME688
Voltage Supervisor + Reset & Boot / IO Button
Battery Charge Level
RTC Module DS3231SN
Test Pads
Qwiic / Stemma QT
SPI ESD Protection Lines
External NOR Flash 64MB
OpenBook Schematic
drawn by: Matei Mantu

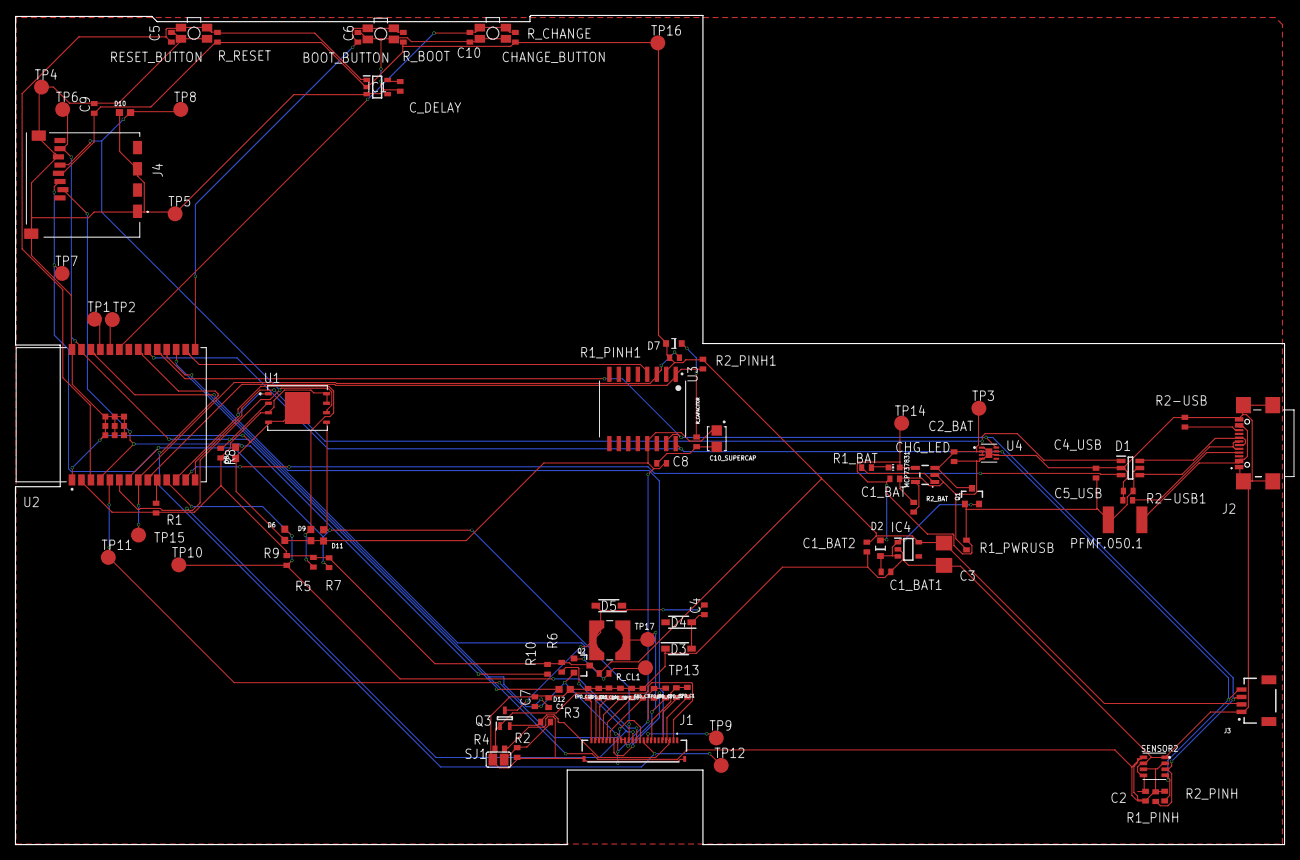
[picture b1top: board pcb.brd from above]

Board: 2 copper layers, 170.2 x 111.2 mm, 103 parts (0 on the bottom side), 56 nets.

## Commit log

2025-04-06 Create LICENSE
2025-04-06 Add project
2025-04-06 Update README.md
    Add BOM
2025-04-06 Add block diagram
2025-04-06 Add front face picture
2025-04-06 Add ESP32 schematic image
2025-04-06 Update README.md
    Clear BOM
2025-04-06 Update README.md
    Add detailed pin descriptions
2025-04-11 Update README.md
    Add Product overview
2025-04-11 Update README.md
    Add Power consumption estimates

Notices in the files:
parts and their libraries:
COPYRIGHT: Copyright (C) 2024 Ultra Librarian. All rights reserved.
